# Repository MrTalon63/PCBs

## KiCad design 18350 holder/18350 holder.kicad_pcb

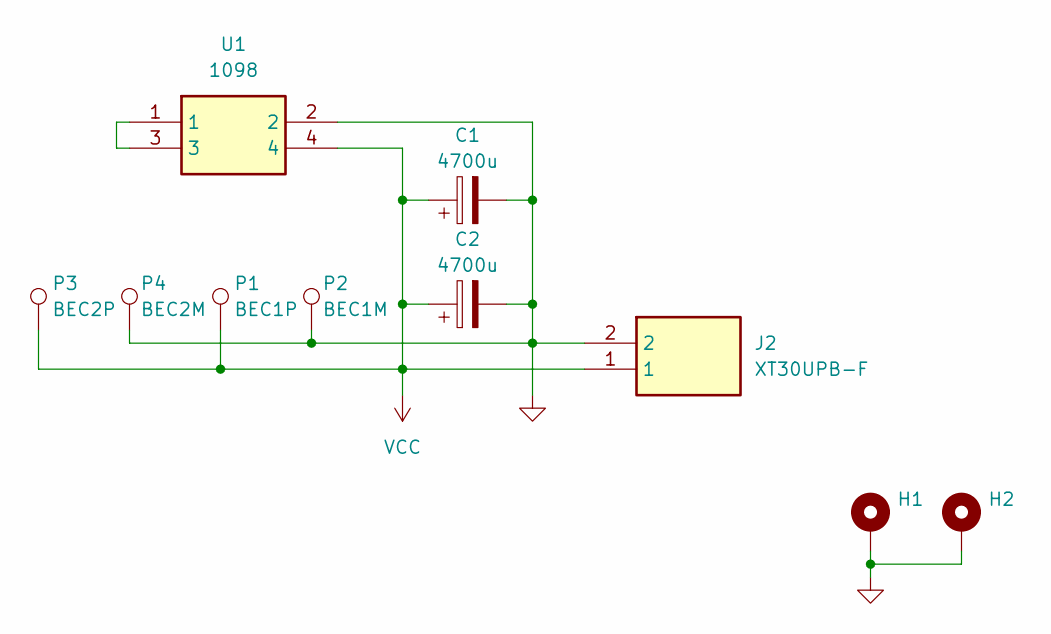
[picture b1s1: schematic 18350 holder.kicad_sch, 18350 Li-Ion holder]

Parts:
C1, C2: 4700u; CP_Radial_D12.5mm_P5.00mm
H1, H2: MountingHole_Pad; MountingHole_2.7mm_M2.5_Pad
J2: XT30UPB-F; XT30UPBF; Manufacturer_Part_Number XT30UPB-F
P1: BEC1P; Pin_D1.3mm_L11.0mm_LooseFit
P2: BEC1M; Pin_D1.3mm_L11.0mm_LooseFit
P3: BEC2P; Pin_D1.3mm_L11.0mm_LooseFit
P4: BEC2M; Pin_D1.3mm_L11.0mm_LooseFit
U1: 1098; Mouser Part Number 534-1098

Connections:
GND: C1.2, C2.2, H1.1, H2.1, J2.2, P2.1, P4.1, U1.2
unnamed: U1.1, U1.3
VCC: C1.1, C2.1, J2.1, P1.1, P3.1, U1.4

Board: 2 copper layers, 10 parts (0 on the bottom side), 3 nets, no tracks yet.

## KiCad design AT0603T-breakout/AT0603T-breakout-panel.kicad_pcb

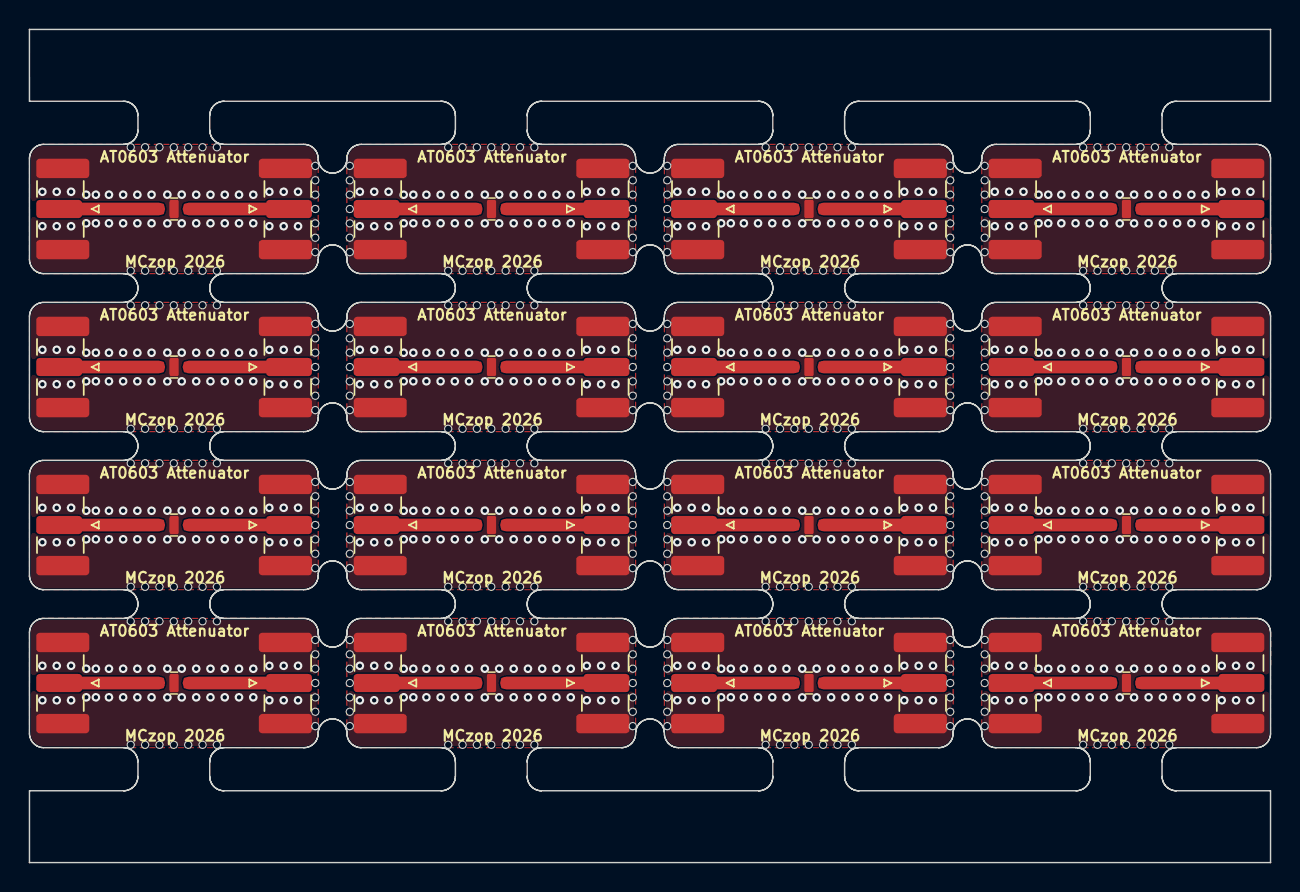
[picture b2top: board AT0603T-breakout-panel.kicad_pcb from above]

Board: 2 copper layers, 86.4 x 58.0 mm, 440 parts (0 on the bottom side), 48 nets.

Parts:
J1, J1#2, J1#3, J1#4, J1#5, J1#6, J1#7, J1#8, J1#9, J1#10, J1#11, J1#12, J1#13, J1#14, J1#15, J1#16: RFI; SMA_Samtec_SMA-J-P-H-ST-EM1_EdgeMount
J2, J2#2, J2#3, J2#4, J2#5, J2#6, J2#7, J2#8, J2#9, J2#10, J2#11, J2#12, J2#13, J2#14, J2#15, J2#16: RFO; SMA_Samtec_SMA-J-P-H-ST-EM1_EdgeMount
KiKit_MB_1_1, KiKit_MB_1_2, KiKit_MB_1_3, KiKit_MB_1_4, KiKit_MB_1_5, KiKit_MB_1_6, KiKit_MB_1_7, KiKit_MB_2_1, KiKit_MB_2_2, KiKit_MB_2_3, KiKit_MB_2_4, KiKit_MB_2_5, KiKit_MB_2_6, KiKit_MB_2_7, KiKit_MB_3_1, KiKit_MB_3_2, KiKit_MB_3_3, KiKit_MB_3_4, KiKit_MB_3_5, KiKit_MB_3_6, KiKit_MB_3_7, KiKit_MB_4_1, KiKit_MB_4_2, KiKit_MB_4_3, KiKit_MB_4_4, KiKit_MB_4_5, KiKit_MB_4_6, KiKit_MB_4_7, KiKit_MB_5_1, KiKit_MB_5_2, KiKit_MB_5_3, KiKit_MB_5_4, KiKit_MB_5_5, KiKit_MB_5_6, KiKit_MB_5_7, KiKit_MB_6_1, KiKit_MB_6_2, KiKit_MB_6_3, KiKit_MB_6_4, KiKit_MB_6_5, KiKit_MB_6_6, KiKit_MB_6_7, KiKit_MB_7_1, KiKit_MB_7_2, KiKit_MB_7_3, KiKit_MB_7_4, KiKit_MB_7_5, KiKit_MB_7_6, KiKit_MB_7_7, KiKit_MB_8_1, KiKit_MB_8_2, KiKit_MB_8_3, KiKit_MB_8_4, KiKit_MB_8_5, KiKit_MB_8_6, KiKit_MB_8_7, KiKit_MB_9_1, KiKit_MB_9_2, KiKit_MB_9_3, KiKit_MB_9_4, KiKit_MB_9_5, KiKit_MB_9_6, KiKit_MB_9_7, KiKit_MB_10_1, KiKit_MB_10_2, KiKit_MB_10_3, KiKit_MB_10_4, KiKit_MB_10_5, KiKit_MB_10_6, KiKit_MB_10_7, KiKit_MB_11_1, KiKit_MB_11_2, KiKit_MB_11_3, KiKit_MB_11_4, KiKit_MB_11_5, KiKit_MB_11_6, KiKit_MB_11_7, KiKit_MB_12_1, KiKit_MB_12_2, KiKit_MB_12_3, KiKit_MB_12_4, KiKit_MB_12_5, KiKit_MB_12_6, KiKit_MB_12_7, KiKit_MB_13_1, KiKit_MB_13_2, KiKit_MB_13_3, KiKit_MB_13_4, KiKit_MB_13_5, KiKit_MB_13_6, KiKit_MB_13_7, KiKit_MB_14_1, KiKit_MB_14_2, KiKit_MB_14_3, KiKit_MB_14_4, KiKit_MB_14_5, KiKit_MB_14_6, KiKit_MB_14_7, KiKit_MB_15_1, KiKit_MB_15_2, KiKit_MB_15_3, KiKit_MB_15_4, KiKit_MB_15_5, KiKit_MB_15_6, KiKit_MB_15_7, KiKit_MB_16_1, KiKit_MB_16_2, KiKit_MB_16_3, KiKit_MB_16_4, KiKit_MB_16_5, KiKit_MB_16_6, KiKit_MB_16_7, KiKit_MB_17_1, KiKit_MB_17_2, KiKit_MB_17_3, KiKit_MB_17_4, KiKit_MB_17_5, KiKit_MB_17_6, KiKit_MB_17_7, KiKit_MB_18_1, KiKit_MB_18_2, KiKit_MB_18_3, KiKit_MB_18_4, KiKit_MB_18_5, KiKit_MB_18_6, KiKit_MB_18_7, KiKit_MB_19_1, KiKit_MB_19_2, KiKit_MB_19_3, KiKit_MB_19_4, KiKit_MB_19_5, KiKit_MB_19_6, KiKit_MB_19_7, KiKit_MB_20_1, KiKit_MB_20_2, KiKit_MB_20_3, KiKit_MB_20_4, KiKit_MB_20_5, KiKit_MB_20_6, KiKit_MB_20_7, KiKit_MB_21_1, KiKit_MB_21_2, KiKit_MB_21_3, KiKit_MB_21_4, KiKit_MB_21_5, KiKit_MB_21_6, KiKit_MB_21_7, KiKit_MB_22_1, KiKit_MB_22_2, KiKit_MB_22_3, KiKit_MB_22_4, KiKit_MB_22_5, KiKit_MB_22_6, KiKit_MB_22_7, KiKit_MB_23_1, KiKit_MB_23_2, KiKit_MB_23_3, KiKit_MB_23_4, KiKit_MB_23_5, KiKit_MB_23_6, KiKit_MB_23_7, KiKit_MB_24_1, KiKit_MB_24_2, KiKit_MB_24_3, KiKit_MB_24_4, KiKit_MB_24_5, KiKit_MB_24_6, KiKit_MB_24_7, KiKit_MB_25_1, KiKit_MB_25_2, KiKit_MB_25_3, KiKit_MB_25_4, KiKit_MB_25_5, KiKit_MB_25_6, KiKit_MB_25_7, KiKit_MB_26_1, KiKit_MB_26_2, KiKit_MB_26_3, KiKit_MB_26_4, KiKit_MB_26_5, KiKit_MB_26_6, KiKit_MB_26_7, KiKit_MB_27_1, KiKit_MB_27_2, KiKit_MB_27_3, KiKit_MB_27_4, KiKit_MB_27_5, KiKit_MB_27_6, KiKit_MB_27_7, KiKit_MB_28_1, KiKit_MB_28_2, KiKit_MB_28_3, KiKit_MB_28_4, KiKit_MB_28_5, KiKit_MB_28_6, KiKit_MB_28_7, KiKit_MB_29_1, KiKit_MB_29_2, KiKit_MB_29_3, KiKit_MB_29_4, KiKit_MB_29_5, KiKit_MB_29_6, KiKit_MB_29_7, KiKit_MB_30_1, KiKit_MB_30_2, KiKit_MB_30_3, KiKit_MB_30_4, KiKit_MB_30_5, KiKit_MB_30_6, KiKit_MB_30_7, KiKit_MB_31_1, KiKit_MB_31_2, KiKit_MB_31_3, KiKit_MB_31_4, KiKit_MB_31_5, KiKit_MB_31_6, KiKit_MB_31_7, KiKit_MB_32_1, KiKit_MB_32_2, KiKit_MB_32_3, KiKit_MB_32_4, KiKit_MB_32_5, KiKit_MB_32_6, KiKit_MB_32_7, KiKit_MB_33_1, KiKit_MB_33_2, KiKit_MB_33_3, KiKit_MB_33_4, KiKit_MB_33_5, KiKit_MB_33_6, KiKit_MB_33_7, KiKit_MB_34_1, KiKit_MB_34_2, KiKit_MB_34_3, KiKit_MB_34_4, KiKit_MB_34_5, KiKit_MB_34_6, KiKit_MB_34_7, KiKit_MB_35_1, KiKit_MB_35_2, KiKit_MB_35_3, KiKit_MB_35_4, KiKit_MB_35_5, KiKit_MB_35_6, KiKit_MB_35_7, KiKit_MB_36_1, KiKit_MB_36_2, KiKit_MB_36_3, KiKit_MB_36_4, KiKit_MB_36_5, KiKit_MB_36_6, KiKit_MB_36_7, KiKit_MB_37_1, KiKit_MB_37_2, KiKit_MB_37_3, KiKit_MB_37_4, KiKit_MB_37_5, KiKit_MB_37_6, KiKit_MB_37_7, KiKit_MB_38_1, KiKit_MB_38_2, KiKit_MB_38_3, KiKit_MB_38_4, KiKit_MB_38_5, KiKit_MB_38_6, KiKit_MB_38_7, KiKit_MB_39_1, KiKit_MB_39_2, KiKit_MB_39_3, KiKit_MB_39_4, KiKit_MB_39_5, KiKit_MB_39_6, KiKit_MB_39_7, KiKit_MB_40_1, KiKit_MB_40_2, KiKit_MB_40_3, KiKit_MB_40_4, KiKit_MB_40_5, KiKit_MB_40_6, KiKit_MB_40_7, KiKit_MB_41_1, KiKit_MB_41_2, KiKit_MB_41_3, KiKit_MB_41_4, KiKit_MB_41_5, KiKit_MB_41_6, KiKit_MB_41_7, KiKit_MB_42_1, KiKit_MB_42_2, KiKit_MB_42_3, KiKit_MB_42_4, KiKit_MB_42_5, KiKit_MB_42_6, KiKit_MB_42_7, KiKit_MB_43_1, KiKit_MB_43_2, KiKit_MB_43_3, KiKit_MB_43_4, KiKit_MB_43_5, KiKit_MB_43_6, KiKit_MB_43_7, KiKit_MB_44_1, KiKit_MB_44_2, KiKit_MB_44_3, KiKit_MB_44_4, KiKit_MB_44_5, KiKit_MB_44_6, KiKit_MB_44_7, KiKit_MB_45_1, KiKit_MB_45_2, KiKit_MB_45_3, KiKit_MB_45_4, KiKit_MB_45_5, KiKit_MB_45_6, KiKit_MB_45_7, KiKit_MB_46_1, KiKit_MB_46_2, KiKit_MB_46_3, KiKit_MB_46_4, KiKit_MB_46_5, KiKit_MB_46_6, KiKit_MB_46_7, KiKit_MB_47_1, KiKit_MB_47_2, KiKit_MB_47_3, KiKit_MB_47_4, KiKit_MB_47_5, KiKit_MB_47_6, KiKit_MB_47_7, KiKit_MB_48_1, KiKit_MB_48_2, KiKit_MB_48_3, KiKit_MB_48_4, KiKit_MB_48_5, KiKit_MB_48_6, KiKit_MB_48_7, KiKit_MB_49_1, KiKit_MB_49_2, KiKit_MB_49_3, KiKit_MB_49_4, KiKit_MB_49_5, KiKit_MB_49_6, KiKit_MB_49_7, KiKit_MB_50_1, KiKit_MB_50_2, KiKit_MB_50_3, KiKit_MB_50_4, KiKit_MB_50_5, KiKit_MB_50_6, KiKit_MB_50_7, KiKit_MB_51_1, KiKit_MB_51_2, KiKit_MB_51_3, KiKit_MB_51_4, KiKit_MB_51_5, KiKit_MB_51_6, KiKit_MB_51_7, KiKit_MB_52_1, KiKit_MB_52_2, KiKit_MB_52_3, KiKit_MB_52_4, KiKit_MB_52_5, KiKit_MB_52_6, KiKit_MB_52_7, KiKit_MB_53_1, KiKit_MB_53_2, KiKit_MB_53_3, KiKit_MB_53_4, KiKit_MB_53_5, KiKit_MB_53_6, KiKit_MB_53_7, KiKit_MB_54_1, KiKit_MB_54_2, KiKit_MB_54_3, KiKit_MB_54_4, KiKit_MB_54_5, KiKit_MB_54_6, KiKit_MB_54_7, KiKit_MB_55_1, KiKit_MB_55_2, KiKit_MB_55_3, KiKit_MB_55_4, KiKit_MB_55_5, KiKit_MB_55_6, KiKit_MB_55_7, KiKit_MB_56_1, KiKit_MB_56_2, KiKit_MB_56_3, KiKit_MB_56_4, KiKit_MB_56_5, KiKit_MB_56_6, KiKit_MB_56_7: NPTH
U1, U1#2, U1#3, U1#4, U1#5, U1#6, U1#7, U1#8, U1#9, U1#10, U1#11, U1#12, U1#13, U1#14, U1#15, U1#16: AT0603T

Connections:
Board_0-GND: J1#16.2 (Ext), J2.2 (Ext), U1#15.3 (GND)
Board_0-Net-(J1-In): J1#16.1 (In), U1#15.1 (RFI)
Board_0-Net-(J2-In): J2.1 (In), U1#15.2 (RFO)
Board_1-GND: J1#14.2 (Ext), J2#7.2 (Ext), U1#12.3 (GND)
Board_1-Net-(J1-In): J1#14.1 (In), U1#12.1 (RFI)
Board_1-Net-(J2-In): J2#7.1 (In), U1#12.2 (RFO)
Board_2-GND: J1#12.2 (Ext), J2#9.2 (Ext), U1#5.3 (GND)
Board_2-Net-(J1-In): J1#12.1 (In), U1#5.1 (RFI)
Board_2-Net-(J2-In): J2#9.1 (In), U1#5.2 (RFO)
Board_3-GND: J1#9.2 (Ext), J2#5.2 (Ext), U1#9.3 (GND)
Board_3-Net-(J1-In): J1#9.1 (In), U1#9.1 (RFI)
Board_3-Net-(J2-In): J2#5.1 (In), U1#9.2 (RFO)
Board_4-GND: J1#4.2 (Ext), J2#14.2 (Ext), U1#7.3 (GND)
Board_4-Net-(J1-In): J1#4.1 (In), U1#7.1 (RFI)
Board_4-Net-(J2-In): J2#14.1 (In), U1#7.2 (RFO)
Board_5-GND: J1#3.2 (Ext), J2#10.2 (Ext), U1#8.3 (GND)
Board_5-Net-(J1-In): J1#3.1 (In), U1#8.1 (RFI)
Board_5-Net-(J2-In): J2#10.1 (In), U1#8.2 (RFO)
Board_6-GND: J1#2.2 (Ext), J2#13.2 (Ext), U1#6.3 (GND)
Board_6-Net-(J1-In): J1#2.1 (In), U1#6.1 (RFI)
Board_6-Net-(J2-In): J2#13.1 (In), U1#6.2 (RFO)
Board_7-GND: J1#13.2 (Ext), J2#12.2 (Ext), U1.3 (GND)
Board_7-Net-(J1-In): J1#13.1 (In), U1.1 (RFI)
Board_7-Net-(J2-In): J2#12.1 (In), U1.2 (RFO)
Board_8-GND: J1#5.2 (Ext), J2#16.2 (Ext), U1#2.3 (GND)
Board_8-Net-(J1-In): J1#5.1 (In), U1#2.1 (RFI)
Board_8-Net-(J2-In): J2#16.1 (In), U1#2.2 (RFO)
Board_9-GND: J1.2 (Ext), J2#2.2 (Ext), U1#16.3 (GND)
Board_9-Net-(J1-In): J1.1 (In), U1#16.1 (RFI)
Board_9-Net-(J2-In): J2#2.1 (In), U1#16.2 (RFO)
Board_10-GND: J1#11.2 (Ext), J2#6.2 (Ext), U1#11.3 (GND)
Board_10-Net-(J1-In): J1#11.1 (In), U1#11.1 (RFI)
Board_10-Net-(J2-In): J2#6.1 (In), U1#11.2 (RFO)
Board_11-GND: J1#7.2 (Ext), J2#11.2 (Ext), U1#4.3 (GND)
Board_11-Net-(J1-In): J1#7.1 (In), U1#4.1 (RFI)
Board_11-Net-(J2-In): J2#11.1 (In), U1#4.2 (RFO)
Board_12-GND: J1#8.2 (Ext), J2#3.2 (Ext), U1#3.3 (GND)
Board_12-Net-(J1-In): J1#8.1 (In), U1#3.1 (RFI)
Board_12-Net-(J2-In): J2#3.1 (In), U1#3.2 (RFO)
Board_13-GND: J1#15.2 (Ext), J2#4.2 (Ext), U1#10.3 (GND)
Board_13-Net-(J1-In): J1#15.1 (In), U1#10.1 (RFI)
Board_13-Net-(J2-In): J2#4.1 (In), U1#10.2 (RFO)
Board_14-GND: J1#6.2 (Ext), J2#15.2 (Ext), U1#14.3 (GND)
Board_14-Net-(J1-In): J1#6.1 (In), U1#14.1 (RFI)
Board_14-Net-(J2-In): J2#15.1 (In), U1#14.2 (RFO)
Board_15-GND: J1#10.2 (Ext), J2#8.2 (Ext), U1#13.3 (GND)
Board_15-Net-(J1-In): J1#10.1 (In), U1#13.1 (RFI)
Board_15-Net-(J2-In): J2#8.1 (In), U1#13.2 (RFO)

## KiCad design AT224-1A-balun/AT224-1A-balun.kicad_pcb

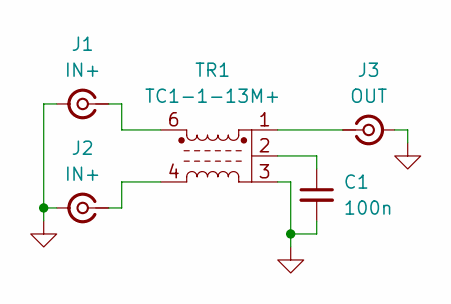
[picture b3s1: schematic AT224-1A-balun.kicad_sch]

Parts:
C1: 100n; C_0402_1005Metric
J1, J2: IN+; SMA_Samtec_SMA-J-P-H-ST-EM1_EdgeMount
J3: OUT; SMA_Samtec_SMA-J-P-H-ST-EM1_EdgeMount
TR1: TC1-1-13M+; Transformer_MiniCircuits_AT224-1A

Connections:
GND: C1.2, J1.2 (Ext), J2.2 (Ext), J3.2 (Ext), TR1.3
unnamed: C1.1, TR1.2
unnamed: J1.1 (In), TR1.6
unnamed: J2.1 (In), TR1.4
unnamed: J3.1 (In), TR1.1

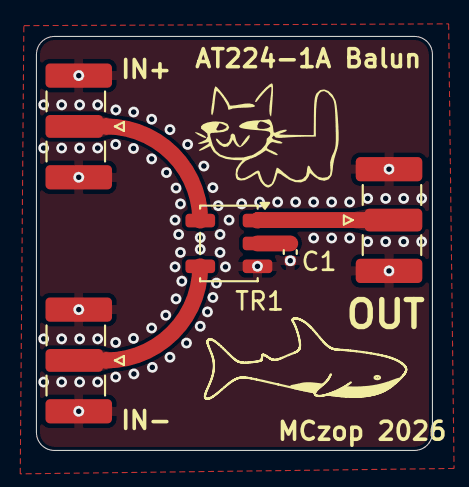
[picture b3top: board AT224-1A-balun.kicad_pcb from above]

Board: 2 copper layers, 22.0 x 23.0 mm, 5 parts (0 on the bottom side), 5 nets.

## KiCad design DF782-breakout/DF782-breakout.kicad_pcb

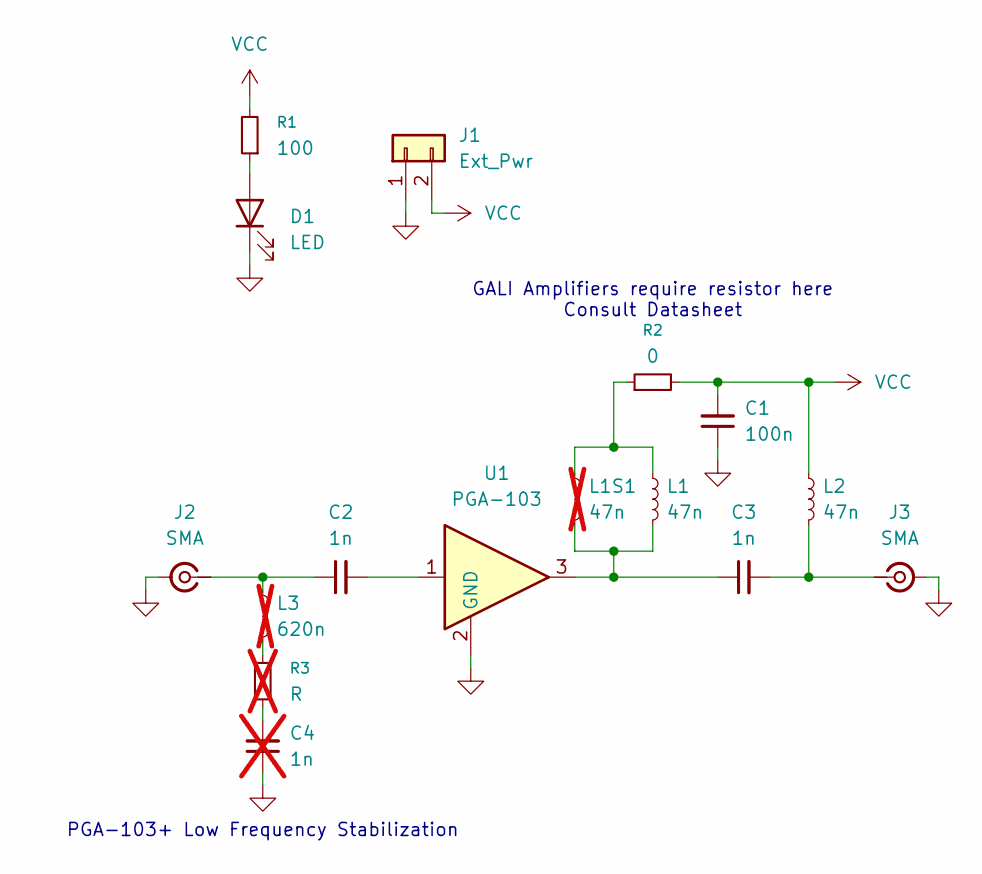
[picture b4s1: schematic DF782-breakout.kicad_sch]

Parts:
C1: 100n; C_0603_1608Metric_Pad1.08x0.95mm_HandSolder
C2, C3: 1n; C_0603_1608Metric_Pad1.08x0.95mm_HandSolder
C4: 1n; C_0603_1608Metric_Pad1.08x0.95mm_HandSolder; not fitted
D1: LED; LED_0805_2012Metric_Pad1.15x1.40mm_HandSolder
J1: Ext_Pwr; PinHeader_1x02_P2.54mm_Vertical
J2, J3: SMA; SMA_Samtec_SMA-J-P-H-ST-EM1_EdgeMount
L1, L2: 47n; L_0603_1608Metric
L1S1: 47n; L_0402_1005Metric; not fitted
L3: 620n; L_0603_1608Metric; not fitted
R1: 100; R_0603_1608Metric
R2: 0; R_0603_1608Metric
R3: R; R_0603_1608Metric; not fitted
U1: PGA-103; SOT-89-3

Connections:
GND: C1.1, C4.1, D1.1 (K), J1.1, J2.2 (Ext), J3.2 (Ext), U1.2 (GND)
unnamed: C2.2, U1.1
unnamed: C3.1, L1.2, L1S1.2, U1.3
unnamed: C4.2, R3.2
unnamed: D1.2 (A), R1.1
unnamed: C2.1, J2.1 (In), L3.1
unnamed: C3.2, J3.1 (In), L2.2
unnamed: L1.1, L1S1.1, R2.1
unnamed: L3.2, R3.1
VCC: C1.2, J1.2, L2.1, R1.2, R2.2

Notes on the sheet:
PGA-103+ Low Frequency Stabilization
GALI Amplifiers require resistor here Consult Datasheet

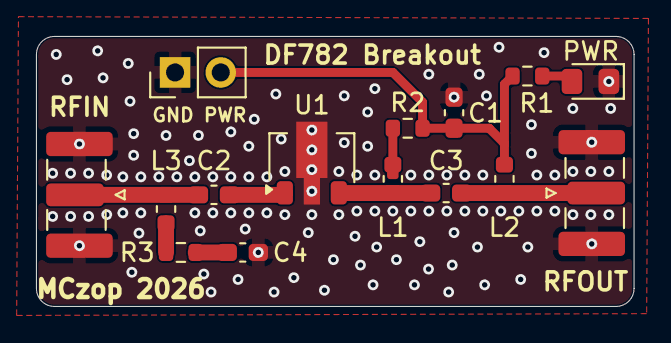
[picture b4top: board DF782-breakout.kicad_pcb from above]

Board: 2 copper layers, 33.2 x 15.0 mm, 16 parts (0 on the bottom side), 10 nets.

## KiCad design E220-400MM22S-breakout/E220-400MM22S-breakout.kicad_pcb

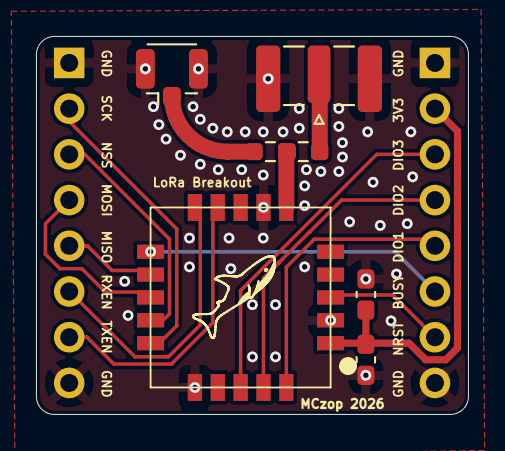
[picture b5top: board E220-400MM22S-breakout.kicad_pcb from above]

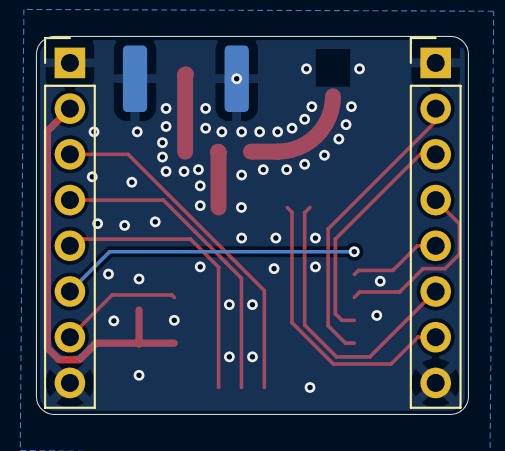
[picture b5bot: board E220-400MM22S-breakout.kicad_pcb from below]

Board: 2 copper layers, 24.0 x 21.0 mm, 9 parts (2 on the bottom side), 16 nets.

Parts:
C1, C2: 100n; C_0603_1608Metric_Pad1.08x0.95mm_HandSolder
J1: SMA; SMA_Samtec_SMA-J-P-H-ST-EM1_EdgeMount
J2: Ufl; U.FL_Hirose_U.FL-R-SMT-1_Vertical
J3, J4: Pinout; PinHeader_1x08_P2.54mm_Vertical
R1, R2: 0; R_0603_1608Metric_Pad0.98x0.95mm_HandSolder
U1: E220-400MM22S; Ebyte MM series

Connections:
+3V3: C1.2, C2.2, J3.2, U1.1 (VCC)
/BUSY: J3.6, U1.11 (BUSY)
/DIO1: J3.5, U1.20 (DIO1)
/DIO2: J3.4, U1.19 (DIO2)
/DIO3: J3.3, U1.18 (DIO3)
/MISO: J4.5, U1.12 (MISO)
/MOSI: J4.4, U1.13 (MOSI)
/NRST: J3.7, U1.3 (NRST)
/NSS: J4.3, U1.14 (NSS)
/RXEN: J4.6, U1.10 (RXEN)
/SCK: J4.2, U1.15 (SCK)
/TXEN: J4.7, U1.9 (TXEN)
GND: C1.1, C2.1, J1.2 (Ext), J2.2 (Ext), J3.1, J3.8, J4.1, J4.8, U1.2 (GND), U1.7 (GND), U1.16 (GND)
unnamed: J1.1 (In), R1.2
unnamed: J2.1 (In), R2.2
unnamed: R1.1, R2.1, U1.6 (ANT)

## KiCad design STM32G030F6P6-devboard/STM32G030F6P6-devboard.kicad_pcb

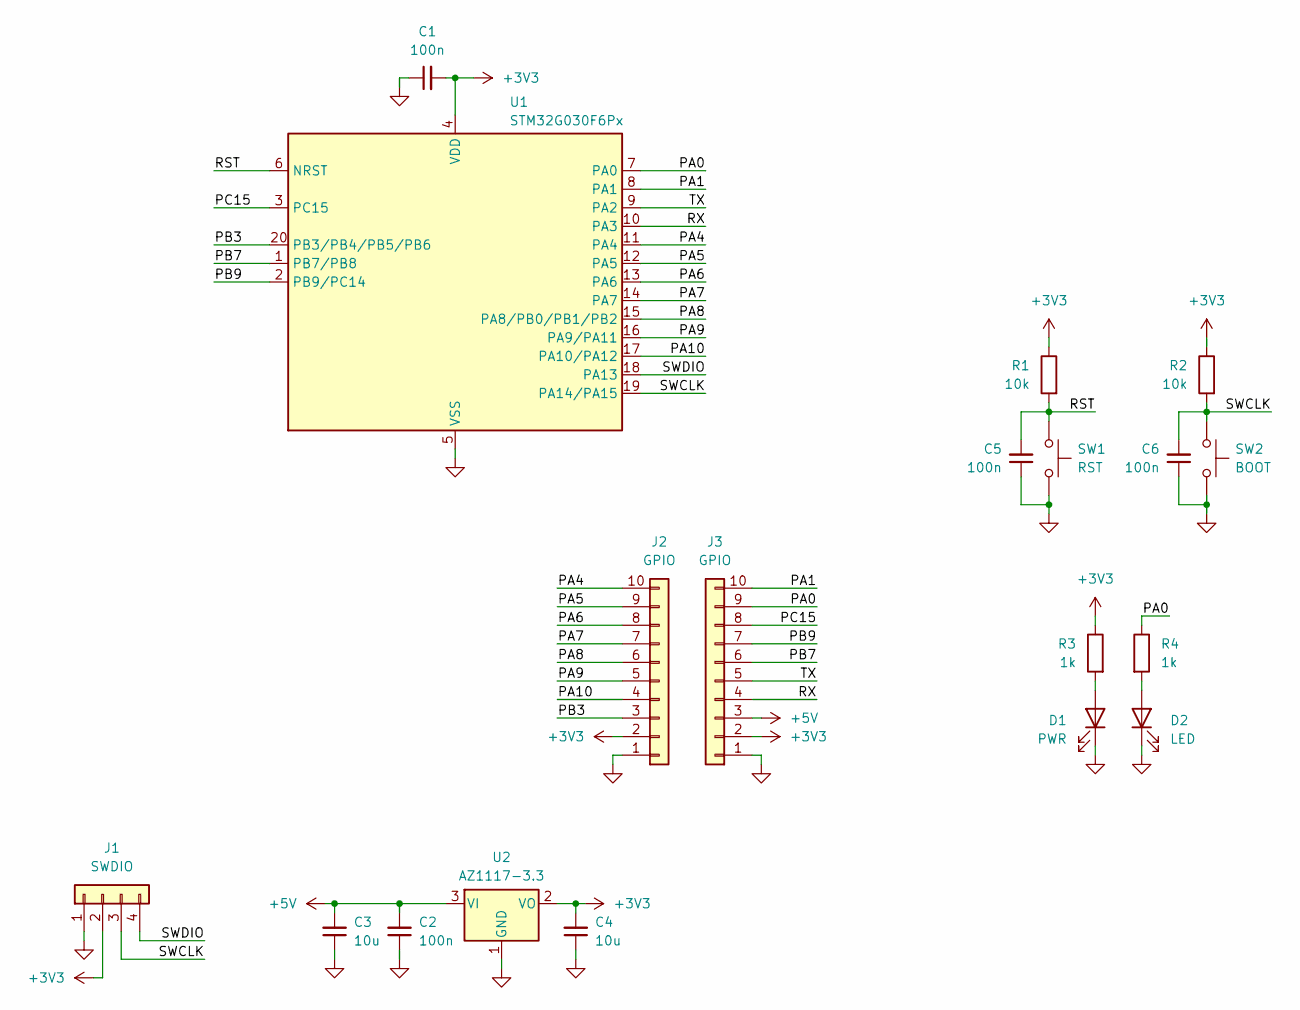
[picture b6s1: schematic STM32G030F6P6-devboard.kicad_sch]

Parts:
C1, C2, C5, C6: 100n; C_0603_1608Metric_Pad1.08x0.95mm_HandSolder
C3, C4: 10u; C_0603_1608Metric_Pad1.08x0.95mm_HandSolder
D1: PWR; LED_0805_2012Metric_Pad1.15x1.40mm_HandSolder
D2: LED; LED_0805_2012Metric_Pad1.15x1.40mm_HandSolder
J1: SWDIO; PinHeader_1x04_P2.54mm_Vertical
J2, J3: GPIO; PinHeader_1x10_P2.54mm_Vertical
R1, R2: 10k; R_0603_1608Metric_Pad0.98x0.95mm_HandSolder
R3, R4: 1k; R_0603_1608Metric_Pad0.98x0.95mm_HandSolder
SW1: RST; KLS7TS6611
SW2: BOOT; KLS7TS6611
U1: STM32G030F6Px; TSSOP-20_4.4x6.5mm_P0.65mm
U2: AZ1117-3.3; SOT-223-3_TabPin2

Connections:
+3V3: C1.2, C4.2, J1.2, J2.2, J3.2, R1.1, R2.1, R3.1, U1.4 (VDD), U2.2 (VO)
+5V: C2.2, C3.2, J3.3, U2.3 (VI)
/PA0: J3.9, R4.1, U1.7 (PA0)
/PA1: J3.10, U1.8 (PA1)
/PA4: J2.10, U1.11 (PA4)
/PA5: J2.9, U1.12 (PA5)
/PA6: J2.8, U1.13 (PA6)
/PA7: J2.7, U1.14 (PA7)
/PA8: J2.6, U1.15 (PA8/PB0/PB1/PB2)
/PA9: J2.5, U1.16 (PA9/PA11)
/PA10: J2.4, U1.17 (PA10/PA12)
/PB3: J2.3, U1.20 (PB3/PB4/PB5/PB6)
/PB7: J3.6, U1.1 (PB7/PB8)
/PB9: J3.7, U1.2 (PB9/PC14)
/PC15: J3.8, U1.3 (PC15)
/RST: C5.2, R1.2, SW1.1, U1.6 (NRST)
/RX: J3.4, U1.10 (PA3)
/SWCLK: C6.2, J1.3, R2.2, SW2.1, U1.19 (PA14/PA15)
/SWDIO: J1.4, U1.18 (PA13)
/TX: J3.5, U1.9 (PA2)
GND: C1.1, C2.1, C3.1, C4.1, C5.1, C6.1, D1.1 (K), D2.1 (K), J1.1, J2.1, J3.1, SW1.2, SW2.2, U1.5 (VSS), U2.1 (GND)
unnamed: D1.2 (A), R3.2
unnamed: D2.2 (A), R4.2

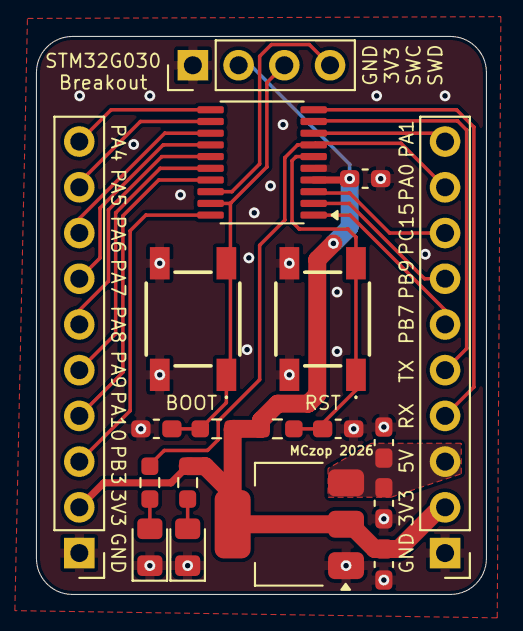
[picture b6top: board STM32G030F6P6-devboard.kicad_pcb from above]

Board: 2 copper layers, 25.0 x 31.0 mm, 19 parts (0 on the bottom side), 23 nets.

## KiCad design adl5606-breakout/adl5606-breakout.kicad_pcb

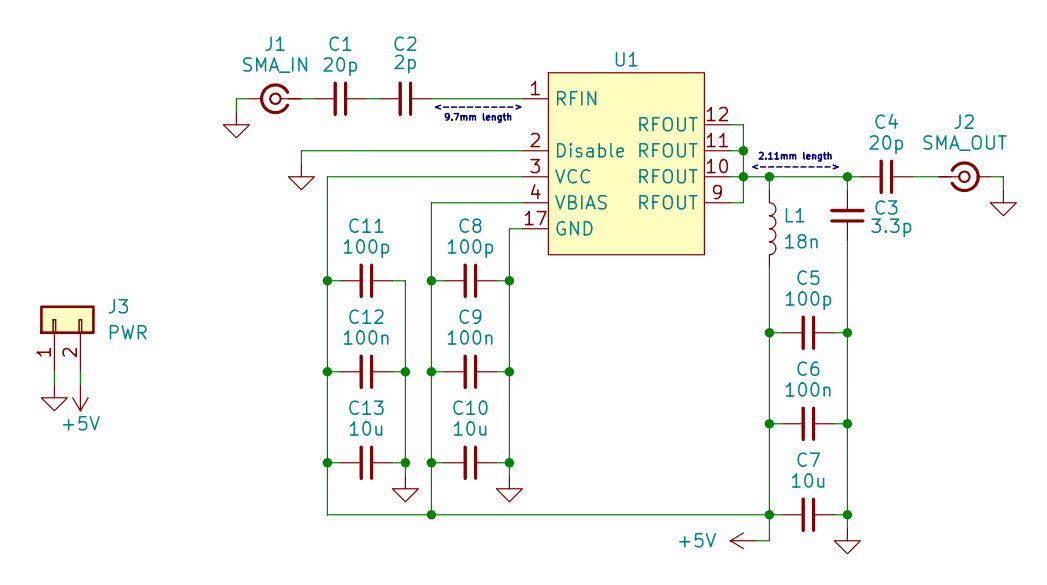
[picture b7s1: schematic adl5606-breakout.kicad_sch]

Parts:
C1, C4: 20p; C_0603_1608Metric_Pad1.08x0.95mm_HandSolder
C2: 2p; C_0603_1608Metric_Pad1.08x0.95mm_HandSolder
C3: 3.3p; C_0603_1608Metric_Pad1.08x0.95mm_HandSolder
C5, C8, C11: 100p; C_0603_1608Metric_Pad1.08x0.95mm_HandSolder
C6, C9, C12: 100n; C_0603_1608Metric_Pad1.08x0.95mm_HandSolder
C7, C10, C13: 10u; C_0603_1608Metric_Pad1.08x0.95mm_HandSolder
J1: SMA_IN; SMA_Samtec_SMA-J-P-H-ST-EM1_EdgeMount
J2: SMA_OUT; SMA_Samtec_SMA-J-P-H-ST-EM1_EdgeMount
J3: PWR; PinSocket_1x02_P2.54mm_Vertical
L1: 18n; L_0603_1608Metric_Pad1.05x0.95mm_HandSolder
U1: Analog_LFCSP-16-1EP_4x4mm_P0.65mm_EP2.35x2.35mm

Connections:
+5V: C5.2, C6.2, C7.2, C8.2, C9.2, C10.2, C11.2, C12.2, C13.2, J3.2, L1.2, U1.3 (VCC), U1.4 (VBIAS)
GND: C3.1, C5.1, C6.1, C7.1, C8.1, C9.1, C10.1, C11.1, C12.1, C13.1, J1.2 (Ext), J2.2 (Ext), J3.1, U1.2 (Disable), U1.17 (GND)
unnamed: C1.1, C2.2
unnamed: C3.2, C4.2, L1.1, U1.9 (RFOUT), U1.10 (RFOUT), U1.11 (RFOUT), U1.12 (RFOUT)
unnamed: C1.2, J1.1 (In)
unnamed: C4.1, J2.1 (In)
unnamed: C2.1, U1.1 (RFIN)

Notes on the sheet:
<---------> 9.7mm length
2.11mm length <--------->

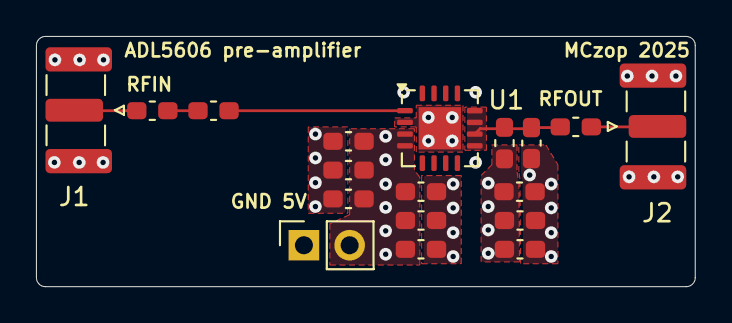
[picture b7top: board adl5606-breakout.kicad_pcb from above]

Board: 6 copper layers, 36.6 x 13.9 mm, 18 parts (0 on the bottom side), 7 nets.

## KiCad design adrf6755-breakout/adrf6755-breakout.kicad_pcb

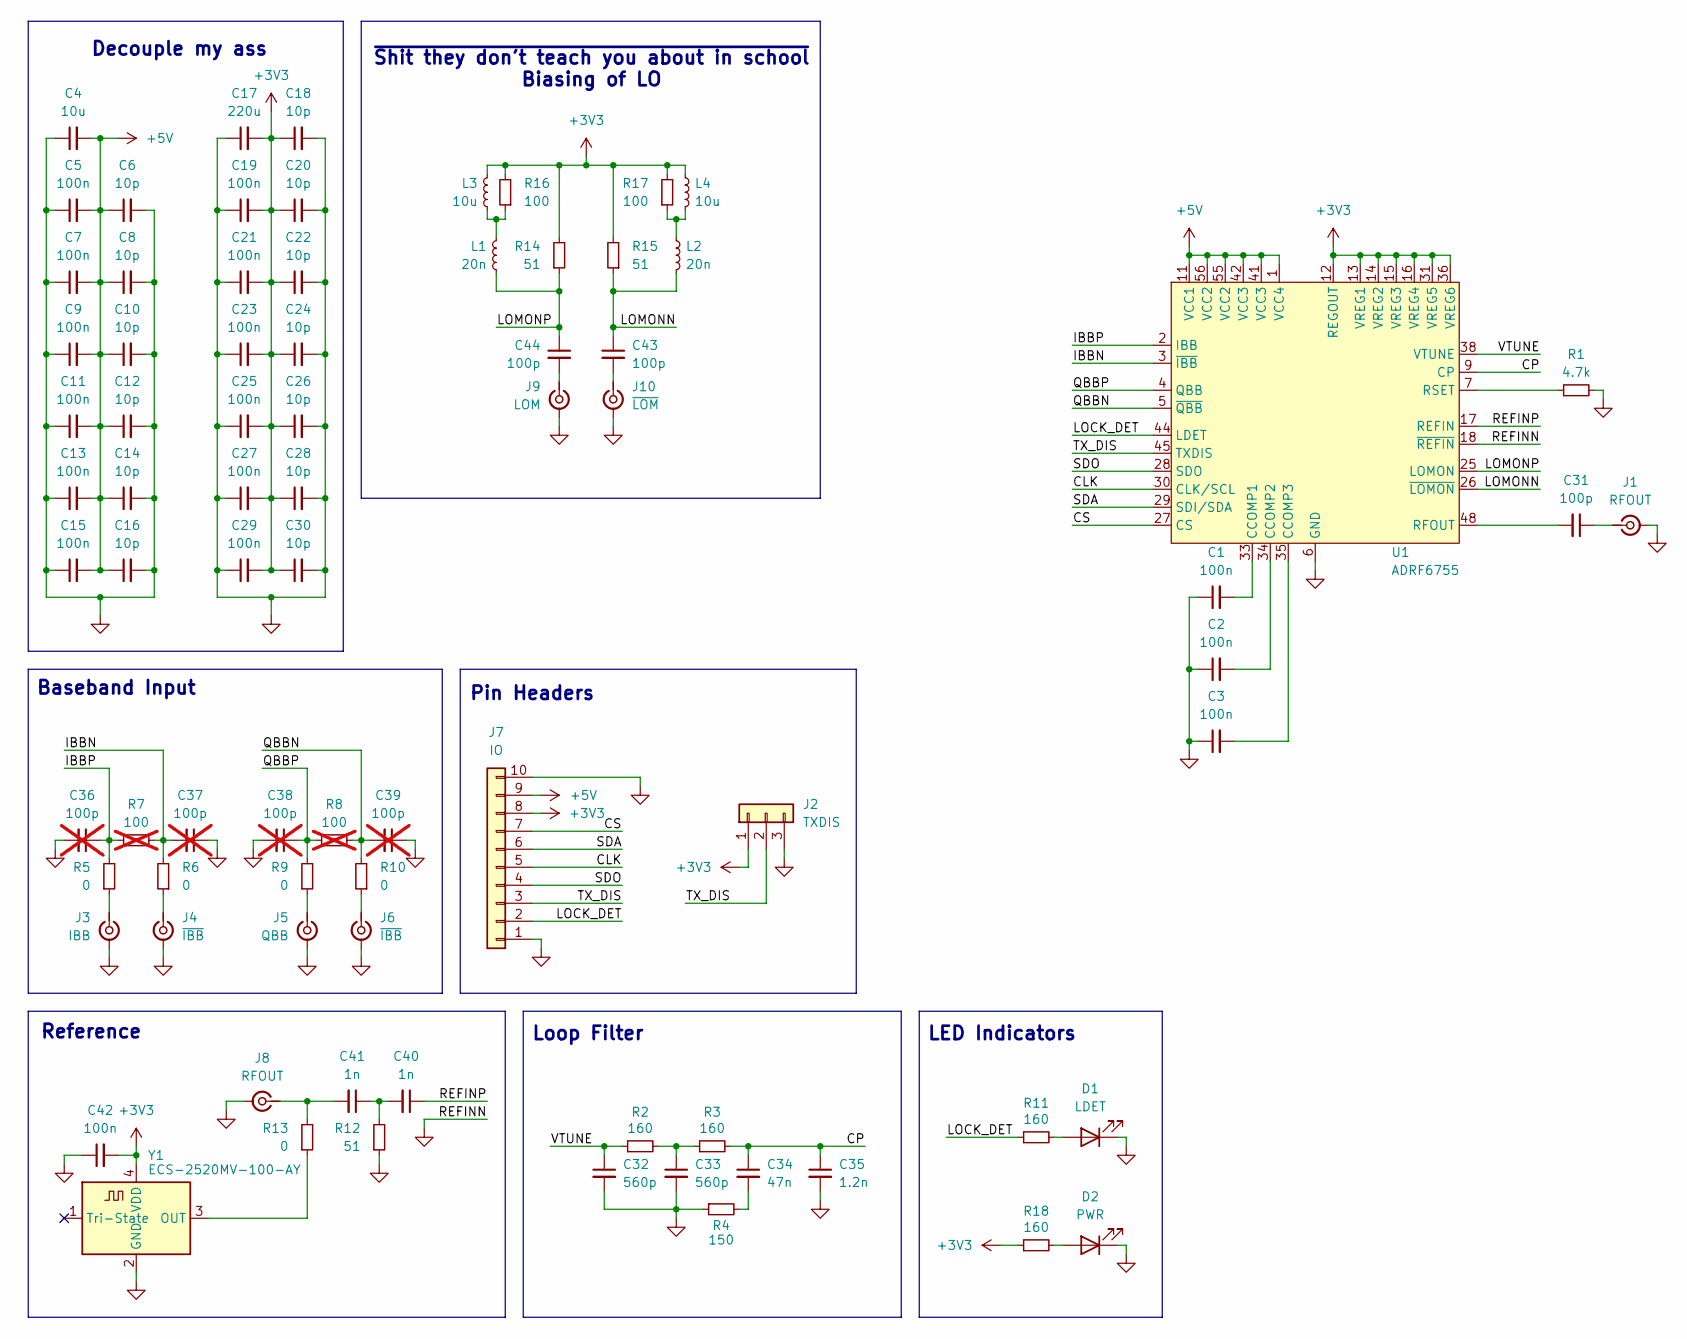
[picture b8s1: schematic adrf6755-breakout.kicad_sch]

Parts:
C1, C2, C3, C5, C7, C9, C11, C13, C15, C19, C21, C23, C25, C27, C29, C42: 100n; C_0402_1005Metric
C4: 10u; C_0805_2012Metric
C6, C8, C10, C12, C14, C16, C18, C20, C22, C24, C26, C28, C30: 10p; C_0402_1005Metric
C17: 220u; CP_EIA-7343-43_Kemet-X
C31, C43, C44: 100p; C_0402_1005Metric
C32, C33: 560p; C_0603_1608Metric
C34: 47n; C_0402_1005Metric
C35: 1.2n; C_0402_1005Metric
C36, C37, C38, C39: 100p; C_0402_1005Metric; not fitted
C40, C41: 1n; C_0402_1005Metric
D1: LDET; LED_0805_2012Metric
D2: PWR; LED_0805_2012Metric
J1, J8: RFOUT; SMA_Samtec_SMA-J-P-H-ST-EM1_EdgeMount
J2: TXDIS; PinHeader_1x03_P2.54mm_Vertical
J3: IBB; SMA_Samtec_SMA-J-P-H-ST-EM1_EdgeMount
J4, J6: ~{IBB}; SMA_Samtec_SMA-J-P-H-ST-EM1_EdgeMount
J5: QBB; SMA_Samtec_SMA-J-P-H-ST-EM1_EdgeMount
J7: IO; PinHeader_1x10_P2.54mm_Vertical
J9: LOM; SMA_Samtec_SMA-J-P-H-ST-EM1_EdgeMount
J10: ~{LOM}; SMA_Samtec_SMA-J-P-H-ST-EM1_EdgeMount
L1, L2: 20n; L_0603_1608Metric
L3, L4: 10u; L_0603_1608Metric
R1: 4.7k; R_0603_1608Metric
R2, R3, R11, R18: 160; R_0603_1608Metric
R4: 150; R_0603_1608Metric
R5, R6, R9, R10, R13: 0; R_0603_1608Metric
R7, R8: 100; R_0603_1608Metric; not fitted
R12, R14, R15: 51; R_0603_1608Metric
R16, R17: 100; R_0603_1608Metric
U1: ADRF6755; QFN50P800X800X100-57N-D
Y1: ECS-2520MV-100-AY; Oscillator_SMD_ECS_2520MV-xxx-xx-4Pin_2.5x2.0mm

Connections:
+3V3: C17.2, C18.1, C19.2, C20.1, C21.2, C22.1, C23.2, C24.1, C25.2, C26.1, C27.2, C28.1, C29.2, C30.1, C42.2, J2.1, J7.8, L3.1, L4.1, R14.2, R15.2, R16.2, R17.2, R18.1, U1.12 (REGOUT), U1.13 (VREG1), U1.14 (VREG2), U1.15 (VREG3), U1.16 (VREG4), U1.31 (VREG5), U1.36 (VREG6), Y1.4 (VDD)
+5V: C4.2, C5.2, C6.1, C7.2, C8.1, C9.2, C10.1, C11.2, C12.1, C13.2, C14.1, C15.2, C16.1, J7.9, U1.1 (VCC4), U1.11 (VCC1), U1.41 (VCC3), U1.42 (VCC3), U1.55 (VCC2), U1.56 (VCC2)
/CLK: J7.5, U1.30 (CLK/SCL)
/CP: C34.1, C35.1, R3.2, U1.9 (CP)
/CS: J7.7, U1.27 (CS)
/IBBN: C37.2, R6.2, R7.2, U1.3 (~IBB)
/IBBP: C36.1, R5.2, R7.1, U1.2 (IBB)
/LOMONN: C43.1, L2.2, R15.1, U1.26 (~LOMON)
/LOMONP: C44.1, L1.2, R14.1, U1.25 (LOMON)
/QBBN: C39.2, R8.2, R10.2, U1.5 (~QBB)
/QBBP: C38.1, R8.1, R9.2, U1.4 (QBB)
/REFINP: C40.1, U1.17 (REFIN)
/SDA: J7.6, U1.29 (SDI/SDA)
/SDO: J7.4, U1.28 (SDO)
/TX_DIS: J2.2, J7.3, U1.45 (TXDIS)
/VTUNE: C32.1, R2.1, U1.38 (VTUNE)
GND: C1.1, C2.1, C3.1, C4.1, C5.1, C6.2, C7.1, C8.2, C9.1, C10.2, C11.1, C12.2, C13.1, C14.2, C15.1, C16.2, C17.1, C18.2, C19.1, C20.2, C21.1, C22.2, C23.1, C24.2, C25.1, C26.2, C27.1, C28.2, C29.1, C30.2, C32.2, C33.2, C35.2, C36.2, C37.1, C38.2, C39.1, C42.1, D1.1 (K), D2.1 (K), J1.2 (Ext), J2.3, J3.2 (Ext), J4.2 (Ext), J5.2 (Ext), J6.2 (Ext), J7.1, J7.10, J8.2 (Ext), J9.2 (Ext), J10.2 (Ext), R1.2, R4.1, R12.1, U1.6 (GND), U1.18 (~REFIN), U1.19 (GND), U1.20 (GND), U1.21 (GND), U1.22 (GND), U1.23 (GND), U1.24 (GND), U1.32 (GND), U1.37 (GND), U1.39 (GND), U1.40 (GND), U1.46 (GND), U1.47 (GND), U1.49 (GND), U1.50 (GND), U1.51 (GND), U1.52 (GND), U1.53 (GND), U1.54 (GND), U1.57 (GND), Y1.2 (GND)
unnamed: C33.1, R2.2, R3.1
unnamed: C34.2, R4.2
unnamed: C40.2, C41.1, R12.2
unnamed: D1.2 (A), R11.2
unnamed: D2.2 (A), R18.2
unnamed: C31.1, J1.1 (In)
unnamed: J3.1 (In), R5.1
unnamed: J4.1 (In), R6.1
unnamed: J5.1 (In), R9.1
unnamed: J6.1 (In), R10.1
unnamed: C41.2, J8.1 (In), R13.2
unnamed: C44.2, J9.1 (In)
unnamed: C43.2, J10.1 (In)
unnamed: L1.1, L3.2, R16.1
unnamed: L2.1, L4.2, R17.1
unnamed: C1.2, U1.33 (CCOMP1)
unnamed: C2.2, U1.34 (CCOMP2)
unnamed: C3.2, U1.35 (CCOMP3)
unnamed: C31.2, U1.48 (RFOUT)
unnamed: R1.1, U1.7 (RSET)
unnamed: R13.1, Y1.3 (OUT)

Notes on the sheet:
Reference
Decouple my ass
~{Shit they don't teach you about in school} Biasing of LO
Loop Filter
Baseband Input
LED Indicators
Pin Headers

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
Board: 2 copper layers, 80 parts (0 on the bottom side), 39 nets, no tracks yet.
